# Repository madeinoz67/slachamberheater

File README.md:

# STR-21-007-SLAChamberHeater

SLA Chamber Heater for Resin Printers

## Project Features

* STR-21-007-SLAChamberHeater
* A starter KiCad project structured similar to <https://hackaday.com/2017/05/18/kicad-best-practises-library-management/>
* A starter documentation structure based on the <https://hutscape.com/pine/> by Sayanee Basu <https://github.com/sayanee> and her great youtube video around hardware documentation <https://youtu.be/uPitFGqjyPU>.

## Resources

Below are some handy resource links.

* [KiCad](https://www.kicad.org/) is a Cross Platform and Open Source Electronics Design Automation suite.
* [cookiecutter-kicad](https://github.com/madeinoz67/cookiecutter-kicad) a cookiecutter template for KiCad Projects.

## Authors

* **Stephen Eaton** - *Initial Work* - [github](https://github.com/madeinoz67)

See also the list of [contributors](https://github.com/madeinoz67/slachamberheater/AUTHORS.rst) who participated in this project.

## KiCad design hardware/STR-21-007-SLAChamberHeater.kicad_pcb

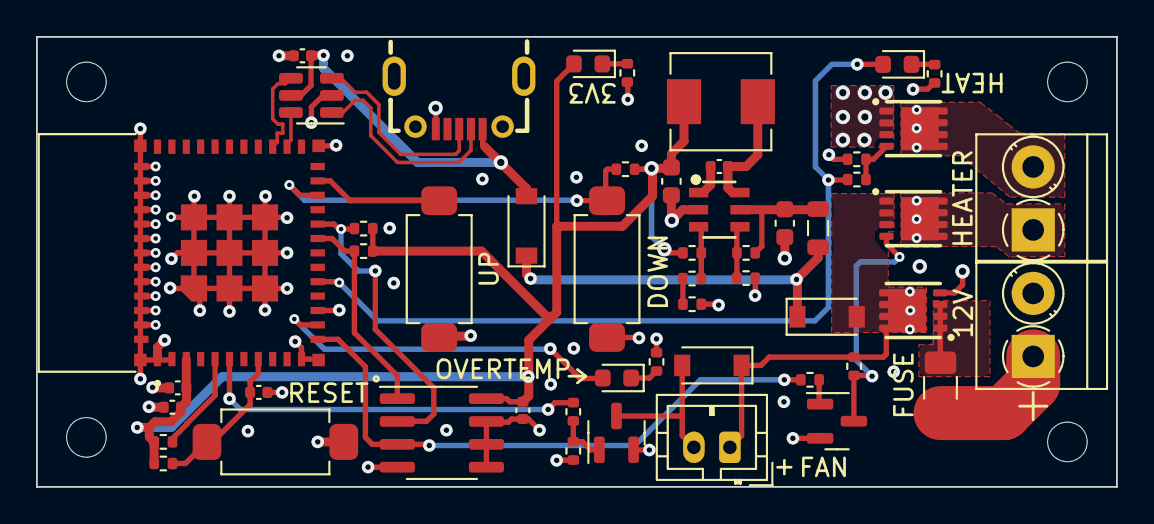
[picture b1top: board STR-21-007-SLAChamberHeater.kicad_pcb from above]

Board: 4 copper layers, 60.0 x 25.0 mm, 56 parts (0 on the bottom side), 36 nets.

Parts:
C101: 10n; C_0402_1005Metric
C102: 10u; C_0603_1608Metric
C103: 22u; C_0603_1608Metric
C201: 10u; C_0402_1005Metric
C202: 1u; C_0402_1005Metric
C203, C204, C301: 100n; C_0402_1005Metric
D101, D102: B5819W; D_SOD-123
D301: 1N4148W; D_SOD-123
F101: 5A; Fuse_1206_3216Metric
FB101: 600@600MHz; L_0805_2012Metric
H1, H2, H3, H4: MountingHole; MountingHole_2.2mm_M2
J101: 2.5mm; TerminalBlock_Phoenix_PT-1,5-2-3.5-H_1x02_P3.50mm_Horizontal
J301: HEATER; TerminalBlock_Phoenix_PT-1,5-2-3.5-H_1x02_P3.50mm_Horizontal
J302: FAN; JST_PH_B2B-PH-K_1x02_P2.00mm_Vertical
L101: 10u; L_Sunlord_MWSA0518_5.4x5.2mm
LED101: Green; LED_0603_1608Metric
LED301: Blue; LED_0603_1608Metric
LED302: Red; LED_0603_1608Metric
Q101, Q302: RU30L30M3; DFN-8_L3.0-W3.0-P0.65-BL
Q301, Q304: BSS138; SOT-23
Q303: RU3070M3; DFN-8_L3.0-W3.0-P0.65-BL
R101: 100K; R_0402_1005Metric
R102: 68K; R_0402_1005Metric
R103: 47K; R_0402_1005Metric
R104: 15K; R_0402_1005Metric
R105: 270; R_0402_1005Metric
R106, R306, R308: 1K5; R_0402_1005Metric
R201, R202, R205, R303, R304, R307: 10K; R_0402_1005Metric
R203, R204: 2k2; R_0402_1005Metric
R301, R302, R305: 100R; R_0402_1005Metric
SW201, SW202, SW401: SW_Push; SW_SMD_SPST_8x3.6
U101: MP2359DJ-LF-Z; SOT-23-6_L2.9-W1.6-P0.95-LS2.8-BL
U201: ESP32-C3-MINI-1-N4
U202: USBLC6-2SC6; SOT-23-6
U301: LM75BDP; SOIC-8_3.9x4.9mm_P1.27mm
USB201: U-F-M5DD-Y-L; MICRO-USB-SMD_MICRO-USB-18

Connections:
12V_FUSED: D101.2 (A), D301.1 (K), J302.1, Q101.5 (D), Q101.6 (D), Q101.7 (D), Q101.8 (D), Q101.9 (D), Q302.1 (S), Q302.2 (S), Q302.3 (S), R303.2
+3V3: C103.1, C201.1, C203.1, C301.1, L101.2, LED101.2 (A), R103.1, R201.1, R202.1, R203.1, R204.1, R205.1, U201.3 (3V3), U301.8 (+Vs)
+12V: F101.1, J101.1
/[1] Power/FUSE_S: F101.2, Q101.1 (S), Q101.2 (S), Q101.3 (S)
/[2] MCU/BOOT: SW202.2, U201.23 (IO9)
/[2] MCU/EN: C202.1, R202.2, SW201.2, U201.8 (EN)
/[2] MCU/USB_CONN_D+: U202.3 (I/O2), USB201.3 (D+)
/[2] MCU/USB_CONN_D-: U202.1 (I/O1), USB201.2 (D-)
/[2] MCU/USB_D+: U201.27 (IO19), U202.4 (I/O2)
/[2] MCU/USB_D-: U201.26 (IO18), U202.6 (I/O1)
/[3] Heater/FAN_CONN_2: D301.2 (A), J302.2, Q304.3 (D)
/[3] Heater/FAN_G: Q304.1 (G), R305.2, R307.2
/[3] Heater/HEAT_CONN_1: J301.1, Q302.5 (D), Q302.6 (D), Q302.7 (D), Q302.8 (D), Q302.9 (D)
/[3] Heater/HEAT_CONN_2: J301.2, Q303.5 (D), Q303.6 (D), Q303.7 (D), Q303.8 (D), Q303.9 (D)
/[3] Heater/HEAT_G: Q303.4 (G), R302.2, R304.2
/[3] Heater/OT_DRV_G: Q301.1 (G), R301.2
/[3] Heater/OT_G: Q301.3 (D), Q302.4 (G), R303.1
BTN1: R205.2, SW401.2, U201.22 (IO8)
BUCK_BST: C101.1, U101.1 (BST)
BUCK_EN: R101.2, R102.1, U101.4 (EN)
BUCK_FB: R103.2, R104.1, U101.3 (FB)
BUCK_IN: C102.1, FB101.2, R101.1, U101.5 (IN)
BUCK_SW: C101.2, L101.1, U101.6 (SW)
FAN: R305.1, U201.6 (IO3)
GND: C102.2, C103.2, C201.2, C202.2, C203.2, C204.2, C301.2, J101.2, Q101.4 (G), Q301.2 (S), Q303.1 (S), Q303.2 (S), Q303.3 (S), Q304.2 (S), R102.2, R105.2, R106.2, R304.1, R306.2, R307.1, R308.2, SW201.1, SW202.1, SW401.1, U101.2 (GND), U201.1 (GND), U201.2 (GND), U201.11 (GND), U201.14 (GND), U201.36 (GND), U201.37 (GND), U201.38 (GND), U201.39 (GND), U201.40 (GND), U201.41 (GND), U201.42 (GND), U201.43 (GND), U201.44 (GND), U201.45 (GND), U201.46 (GND), U201.47 (GND), U201.48 (GND), U201.49_1 (GND), U201.49_2 (GND), U201.49_3 (GND), U201.49_4 (GND), U201.49_5 (GND), U201.49_6 (GND), U201.49_7 (GND), U201.49_8 (GND), U201.49_9 (GND), U201.50 (GND), U201.51 (GND), U201.52 (GND), U201.53 (GND), U202.2 (GND), U301.4 (GND), U301.5 (A2), U301.6 (A1), U301.7 (A0), USB201.5 (GND)
HEATER: LED301.2 (A), R302.1, U201.16 (IO10)
I2C1_SCL: R204.2, U201.20 (IO6), U301.2 (SCL)
I2C1_SDA: R203.2, U201.19 (IO5), U301.1 (SDA)
unnamed: D101.1 (K), D102.1 (K), FB101.1
unnamed: LED101.1 (K), R106.1
unnamed: LED301.1 (K), R306.1
unnamed: LED302.1 (K), R308.1
unnamed: R104.2, R105.1
OVERTEMP: LED302.2 (A), U201.13 (IO1)
VBUS: C204.1, D102.2 (A), U202.5 (VBUS), USB201.1 (VCC)
~INT_OVERTEMP: R301.1, U201.12 (IO0), U301.3 (O.S.)

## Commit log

2022-06-26 initial project commit
2022-06-26 Update Changelog for PR
2022-06-26 Typo
2022-06-26 remove library directory
2022-06-26 Added kicad-library submodule
2022-06-26 updated library
2022-06-27 started sheet
2022-06-29 progress
2022-06-29 updated gitignore
2022-07-04 split out sheets
    Fixed grid
    Added datasheets
2022-07-10 spice model for Heater circuit
2022-07-10 Added .gitignore for KICAD at hardware level
2022-07-10 updated .gitignore
2022-07-10 schematics finished, footprints assigned. Still need to fix foorptints for MOSFETS
2022-07-10 updated.git_ignore
2022-07-10 removed .kicad_prl from repo and added to .gitignore
2022-07-11 footprint update for MOSFETS to PDFN3333
2022-07-15 routing and foot print changes
2022-07-22 updated for kibot
2022-07-22 Added Kibot automatiosn - still testing
2022-07-22 corrected kibot version for kicad 6
2022-07-22 DRC ignores
2022-07-22 DRC filter

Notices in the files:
hardware/STR-21-007-SLAChamberHeater.kicad_pcb:
License: CERN-OHL-P
